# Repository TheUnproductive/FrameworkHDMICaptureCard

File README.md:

> [!Warning]
>
> Content is not proven and subject to change without notice! Send to fab at your own risk. 

This Project aims to bring a native HDMI Capture Card to the Framework architecture.

The PCB design files can be found inside the ExpansionCards/Electrical/KiCad_templates/Expansion_Card_Retrofit Folder.

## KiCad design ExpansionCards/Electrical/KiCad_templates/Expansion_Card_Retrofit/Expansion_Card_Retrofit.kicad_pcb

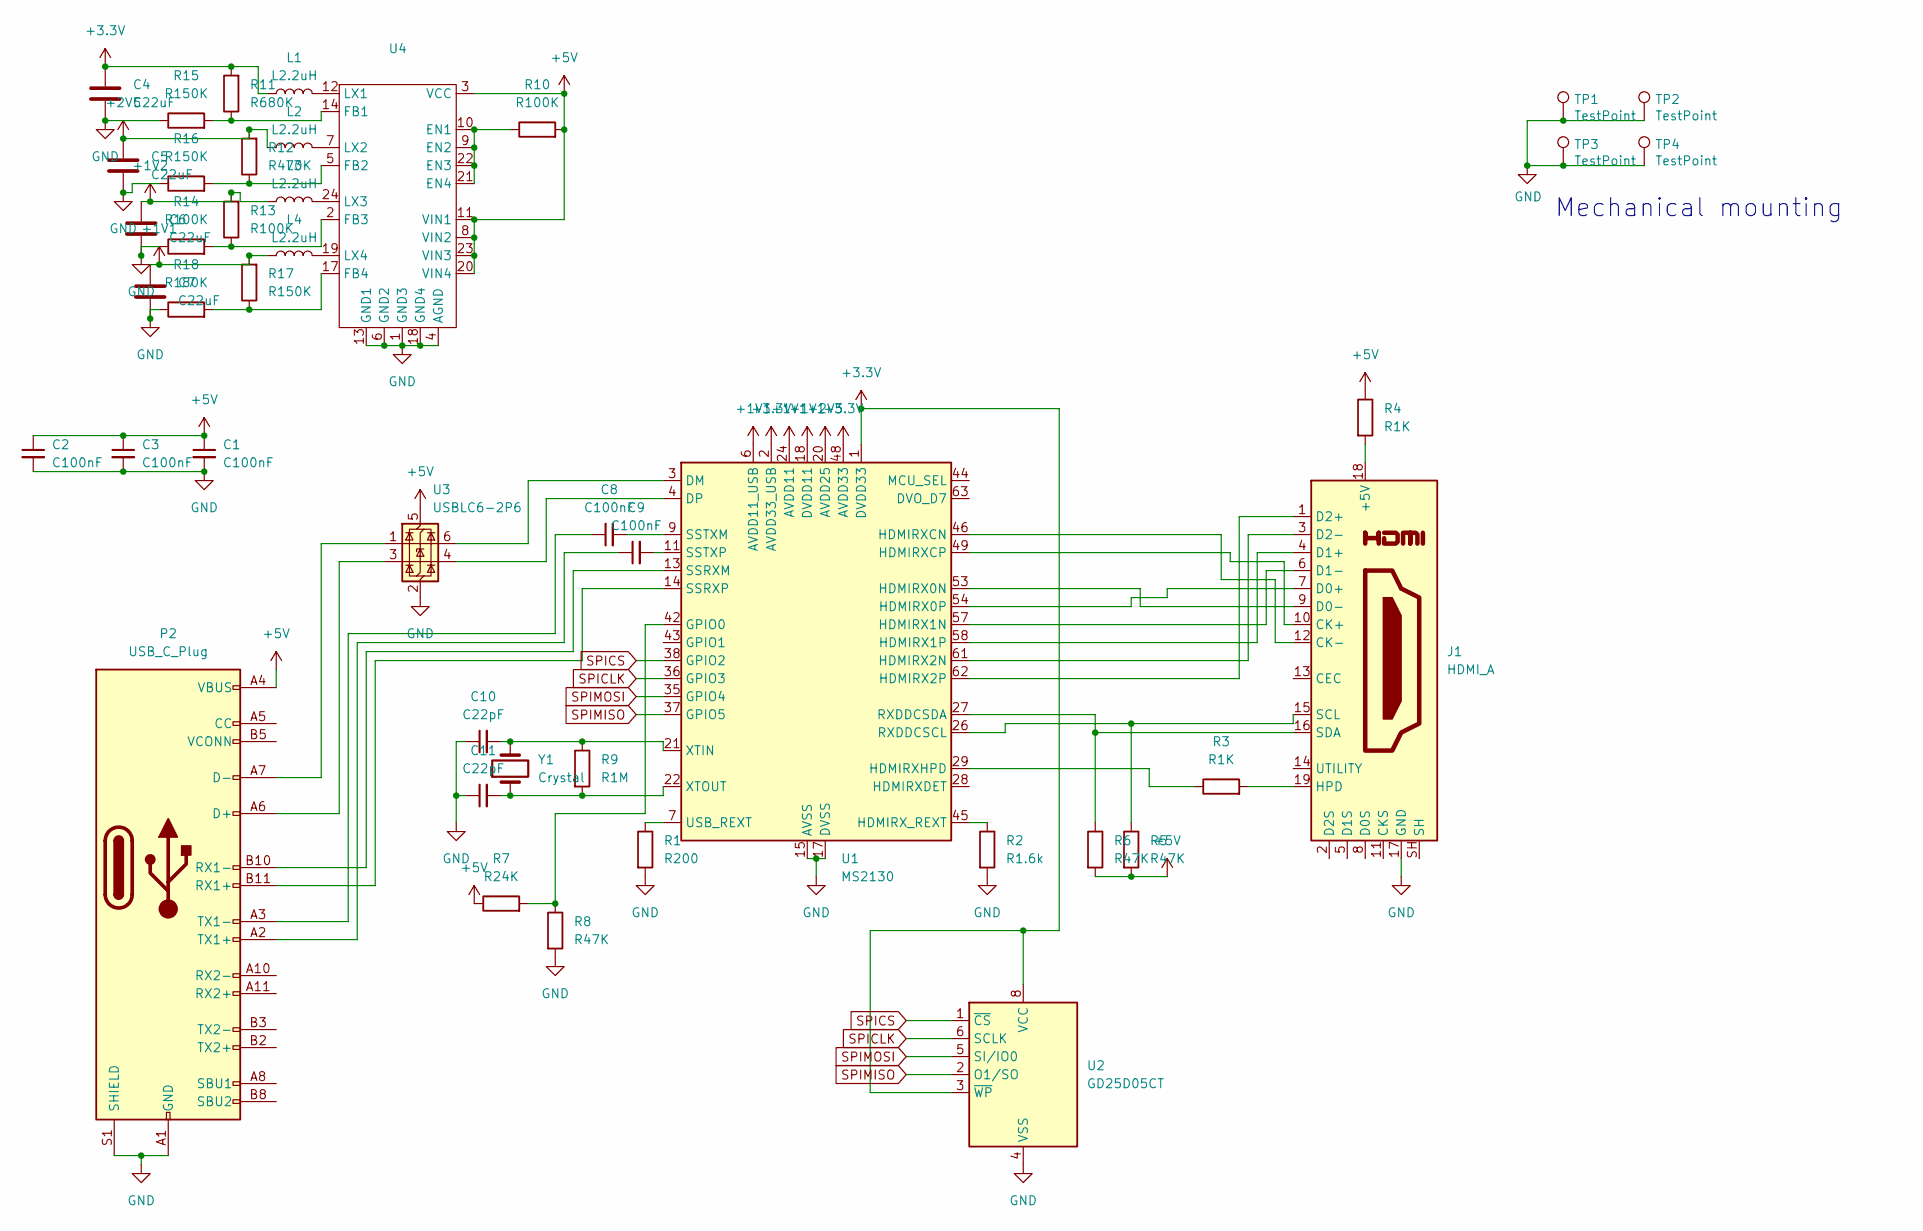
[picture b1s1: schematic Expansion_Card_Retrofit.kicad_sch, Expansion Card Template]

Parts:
C1, C2, C3, C8, C9: C100nF; C_0201_0603Metric
C4, C5, C6, C7: C22uF; C_0201_0603Metric
C10, C11: C22pF; C_0201_0603Metric
J1: HDMI_A; HDMI_A_Amphenol_10029449-x01xLF_Horizontal
L1, L2, L3, L4: L2.2uH; L_0201_0603Metric
P2: USB_C_Plug; USB_C_Plug_Molex_105444
R1: R200; R_0201_0603Metric
R2: R1.6k; R_0201_0603Metric
R3, R4: R1K; R_0201_0603Metric
R5, R6, R8: R47K; R_0201_0603Metric
R7: R24K; R_0201_0603Metric
R9: R1M; R_0201_0603Metric
R10: R100K; R_0201_0603Metric_Pad0.64x0.40mm_HandSolder
R11: R680K; R_0201_0603Metric
R12: R470K; R_0201_0603Metric
R13, R14: R100K; R_0201_0603Metric
R15, R16, R17: R150K; R_0201_0603Metric
R18: R180K; R_0201_0603Metric
TP1, TP2, TP3, TP4: TestPoint; TestPoint_Pad_1.5x1.5mm
U1: MS2130; QFN-64-1EP_9x9mm_P0.5mm_EP5.7x5.7mm
U2: GD25D05CT; JEITA_SOIC-8_3.9x4.9mm_P1.27mm
U3: USBLC6-2P6; SOT-666
U4: HVQFN-24-1EP_4x4mm_P0.5mm_EP2.1x2.1mm
Y1: Crystal; Crystal_SMD_0603-4Pin_6.0x3.5mm

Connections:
+1V1: C7.1, L4.1, R17.2, U1.6 (AVDD11_USB), U1.10 (AVDD11_USB), U1.12 (AVDD11_USB), U1.18 (DVDD11), U1.24 (AVDD11), U1.39 (DVDD11), U1.51 (AVDD11), U1.55 (AVDD11), U1.59 (AVDD11)
+1V2: C6.1, L3.1, R13.2
+2V5: C5.1, L2.1, R12.2, U1.20 (AVDD25), U1.23 (AVDD25), U1.47 (AVDD25)
+3.3V: C4.1, L1.1, R11.2, U1.1 (DVDD33), U1.2 (AVDD33_USB), U1.5 (AVDD33_USB), U1.8 (AVDD33_USB), U1.16 (DVDD33), U1.31 (DVDD33), U1.33 (DVDD33), U1.41 (DVDD33), U1.48 (AVDD33), U1.52 (AVDD33), U1.56 (AVDD33), U1.60 (AVDD33), U2.3 (~WP), U2.8 (VCC)
+5V: C1.1, C2.1, C3.1, P2.A4 (VBUS), P2.A9 (VBUS), P2.B4 (VBUS), P2.B9 (VBUS), R4.1, R5.2, R6.2, R7.1, R10.2, U3.5 (VBUS), U4.3 (VCC), U4.8 (VIN2), U4.11 (VIN1), U4.20 (VIN4), U4.23 (VIN3)
GND: C1.2, C2.2, C3.2, C4.2, C5.2, C6.2, C7.2, C10.1, C11.1, J1.17 (GND), P2.A1 (GND), P2.A12 (GND), P2.B1 (GND), P2.B12 (GND), P2.S1 (SHIELD), R1.2, R2.2, R8.2, R14.1, R15.1, R16.1, R18.1, TP1.1, TP2.1, TP3.1, TP4.1, U1.15 (AVSS), U1.17 (DVSS), U1.19 (AVSS), U1.25 (AVSS), U1.30 (DVSS), U1.32 (DVSS), U1.34 (DVSS), U1.40 (DVSS), U1.50 (AVSS), U1.64 (DVSS), U1.65 (AVSS), U2.4 (VSS), U3.2 (GND), U4.1 (GND3), U4.4 (AGND), U4.6 (GND2), U4.13 (GND1), U4.18 (GND4)
unnamed: J1.18 (+5V), R4.2
unnamed: J1.10 (CK+), U1.49 (HDMIRXCP)
unnamed: J1.12 (CK-), U1.46 (HDMIRXCN)
unnamed: J1.7 (D0+), U1.54 (HDMIRX0P)
unnamed: J1.9 (D0-), U1.53 (HDMIRX0N)
unnamed: J1.4 (D1+), U1.58 (HDMIRX1P)
unnamed: J1.6 (D1-), U1.57 (HDMIRX1N)
unnamed: J1.1 (D2+), U1.62 (HDMIRX2P)
unnamed: J1.3 (D2-), U1.61 (HDMIRX2N)
unnamed: J1.19 (HPD), R3.2
unnamed: J1.15 (SCL), R5.1, U1.26 (RXDDCSCL)
unnamed: J1.16 (SDA), R6.1, U1.27 (RXDDCSDA)
unnamed: P2.A6 (D+), U3.3 (I/O2)
unnamed: P2.A7 (D-), U3.1 (I/O1)
unnamed: P2.B11 (RX1+), U1.14 (SSRXP)
unnamed: P2.B10 (RX1-), U1.13 (SSRXM)
unnamed: C9.1, P2.A2 (TX1+)
unnamed: C8.1, P2.A3 (TX1-)
unnamed: U1.3 (DM), U3.6 (I/O1)
unnamed: U1.4 (DP), U3.4 (I/O2)
unnamed: R7.2, R8.1, U1.42 (GPIO0)
unnamed: R3.1, U1.29 (HDMIRXHPD)
unnamed: R2.1, U1.45 (HDMIRX_REXT)
unnamed: C8.2, U1.9 (SSTXM)
unnamed: C9.2, U1.11 (SSTXP)
unnamed: R1.1, U1.7 (USB_REXT)
unnamed: C10.2, R9.1, U1.21 (XTIN), Y1.2
unnamed: C11.2, R9.2, U1.22 (XTOUT), Y1.1
unnamed: R10.1, U4.9 (EN2), U4.10 (EN1), U4.21 (EN4), U4.22 (EN3)
unnamed: R11.1, R15.2, U4.14 (FB1)
unnamed: R12.1, R16.2, U4.5 (FB2)
unnamed: R13.1, R14.2, U4.2 (FB3)
unnamed: R17.1, R18.2, U4.17 (FB4)
unnamed: L1.2, U4.12 (LX1)
unnamed: L2.2, U4.7 (LX2)
unnamed: L3.2, U4.24 (LX3)
unnamed: L4.2, U4.19 (LX4)
SPICLK: U1.36 (GPIO3), U2.6 (SCLK)
SPICS: U1.38 (GPIO2), U2.1 (~CS)
SPIMISO: U1.37 (GPIO5), U2.2 (O1/SO)
SPIMOSI: U1.35 (GPIO4), U2.5 (SI/IO0)

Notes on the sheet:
Mechanical mounting

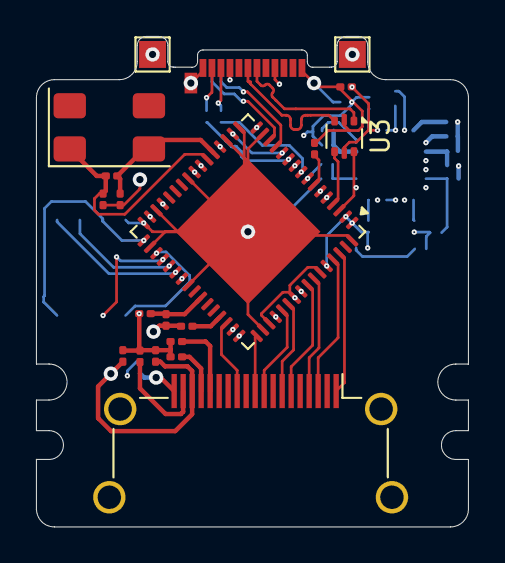
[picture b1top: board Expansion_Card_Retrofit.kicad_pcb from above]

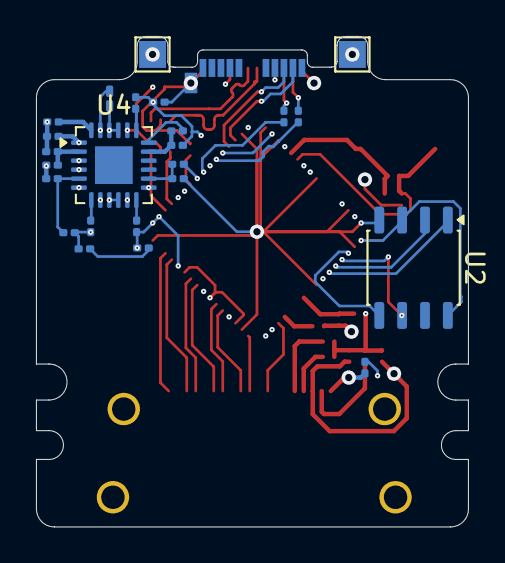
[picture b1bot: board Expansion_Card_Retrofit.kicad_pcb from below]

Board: 4 copper layers, 24.0 x 27.3 mm, 44 parts (24 on the bottom side), 47 nets.

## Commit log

2025-12-31 Add initial files
2026-01-02 Change PCB to 4 Layer and improve routing
2026-01-02 Prepare for gerber export
2026-01-02 Add project description and PCB design location
2026-01-02 Finished PCB design and add gerber files and BOM
2026-01-03 Modified the USB traces to get more closely matching trace lengths
2026-01-05 Add warning about content changes in README
    Added a warning about content being unproven and subject to change.
2026-01-05 Fix typo in warning message in README.md

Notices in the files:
ExpansionCards/Electrical/KiCad_templates/Expansion_Card_Retrofit/Expansion_Card_Retrofit.kicad_pcb:
This work is licensed under a Creative Commons Attribution 4.0 International License
